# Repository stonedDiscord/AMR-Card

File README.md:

# Audio/Modem Riser in KiCad

I have a motherboard with this AMR riser plug and nothing to connect to it.

Modems suck so i will try to design a Audio-Only Riser Module by the Intel specification.
Should make it easy to add S/PDIF to old AC97 motherboards.

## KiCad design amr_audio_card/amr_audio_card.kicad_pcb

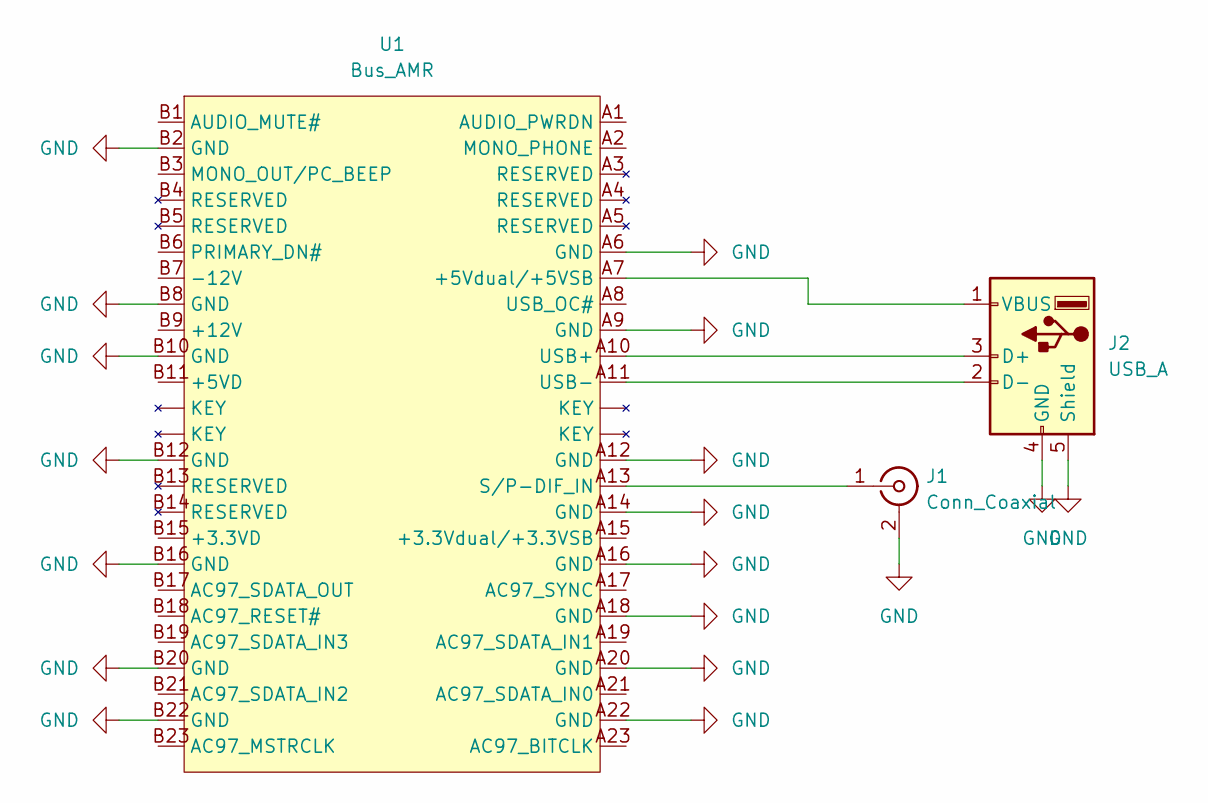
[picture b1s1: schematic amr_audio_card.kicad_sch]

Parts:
J1: Conn_Coaxial; BNC_TEConnectivity_1478035_Horizontal
J2: USB_A; USB_A_Molex_67643_Horizontal
U1: Bus_AMR; BUS_AMR

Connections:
GND: J1.2 (Ext), J2.4 (GND), J2.5 (Shield), U1.A6 (GND), U1.A9 (GND), U1.A12 (GND), U1.A14 (GND), U1.A16 (GND), U1.A18 (GND), U1.A20 (GND), U1.A22 (GND), U1.B2 (GND), U1.B8 (GND), U1.B10 (GND), U1.B12 (GND), U1.B16 (GND), U1.B20 (GND), U1.B22 (GND)
unnamed: J1.1 (In), U1.A13 (S/P-DIF_IN)
unnamed: J2.1 (VBUS), U1.A7 (+5Vdual/+5VSB)
unnamed: J2.2 (D-), U1.A11 (USB-)
unnamed: J2.3 (D+), U1.A10 (USB+)

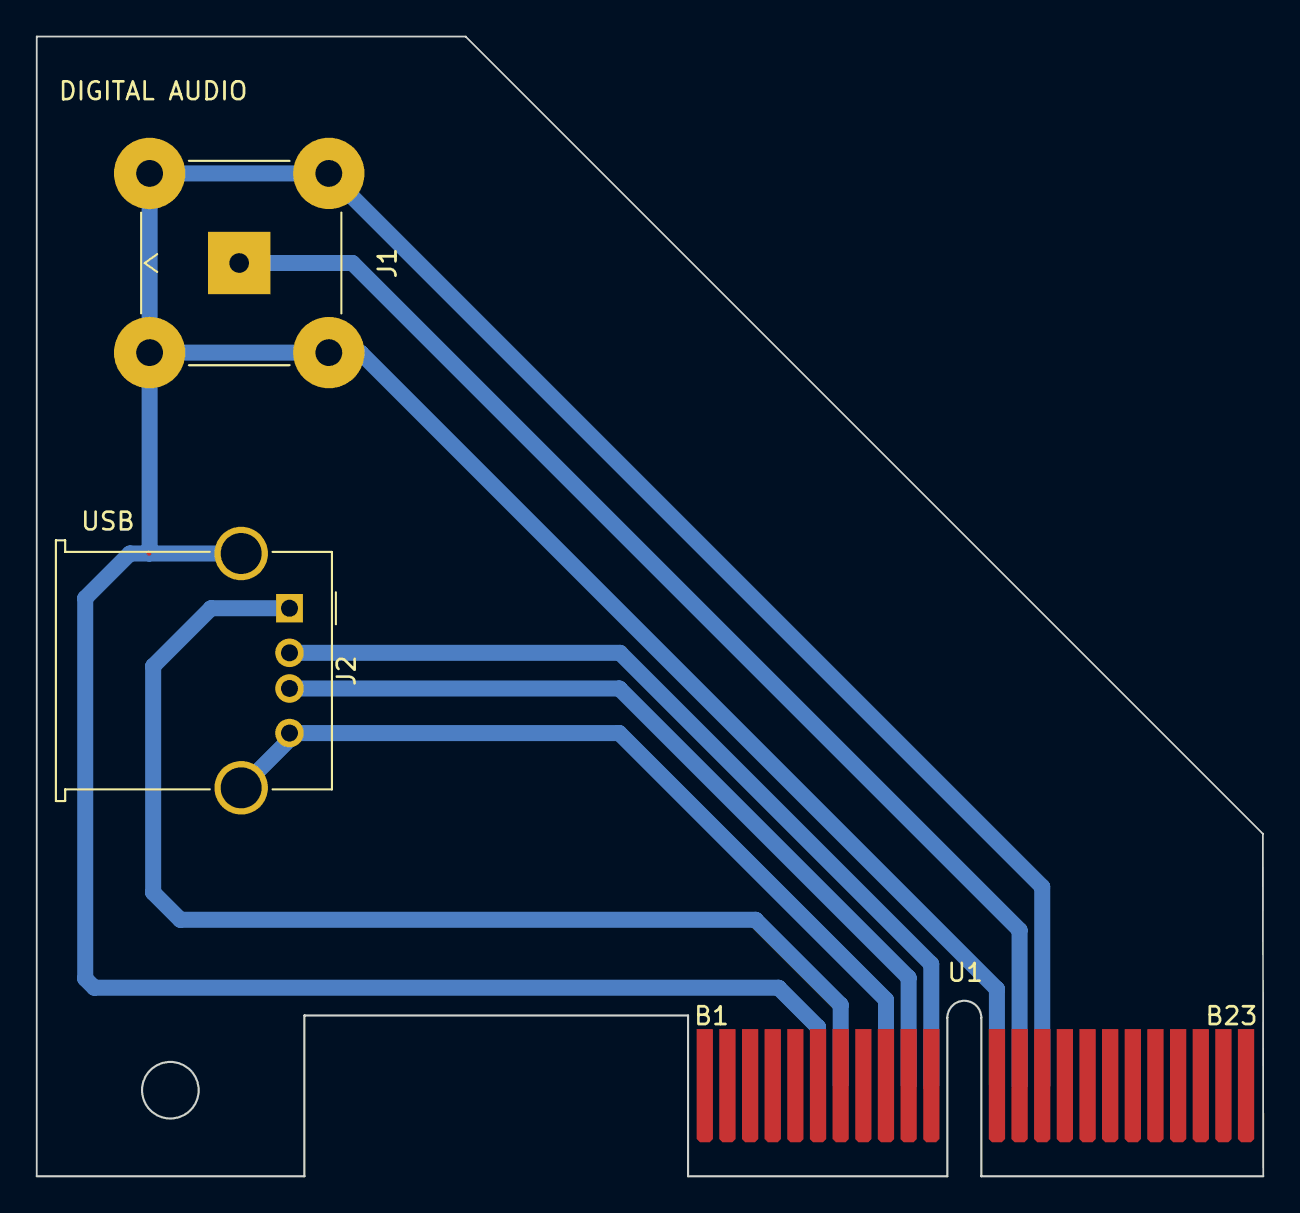
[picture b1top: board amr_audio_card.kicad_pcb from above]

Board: 2 copper layers, 68.8 x 63.9 mm, 3 parts (0 on the bottom side), 5 nets.

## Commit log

2022-06-28 symbol
2022-06-28 card edge footprint
2022-06-28 fix grid
2022-06-28 generate gerbers
2022-06-28 make all the tracks thicker
2022-07-02 yeah i don't need a bunch of empty space fabricated
2022-07-03 generate drill files
2022-07-04 there was no soldermask on the bottom
2022-07-23 remove empty corner
2022-07-23 had it flipped
2022-07-23 update pcb
2022-07-23 gerb
2022-07-23 add an actual RCA jack
2025-05-19 move
